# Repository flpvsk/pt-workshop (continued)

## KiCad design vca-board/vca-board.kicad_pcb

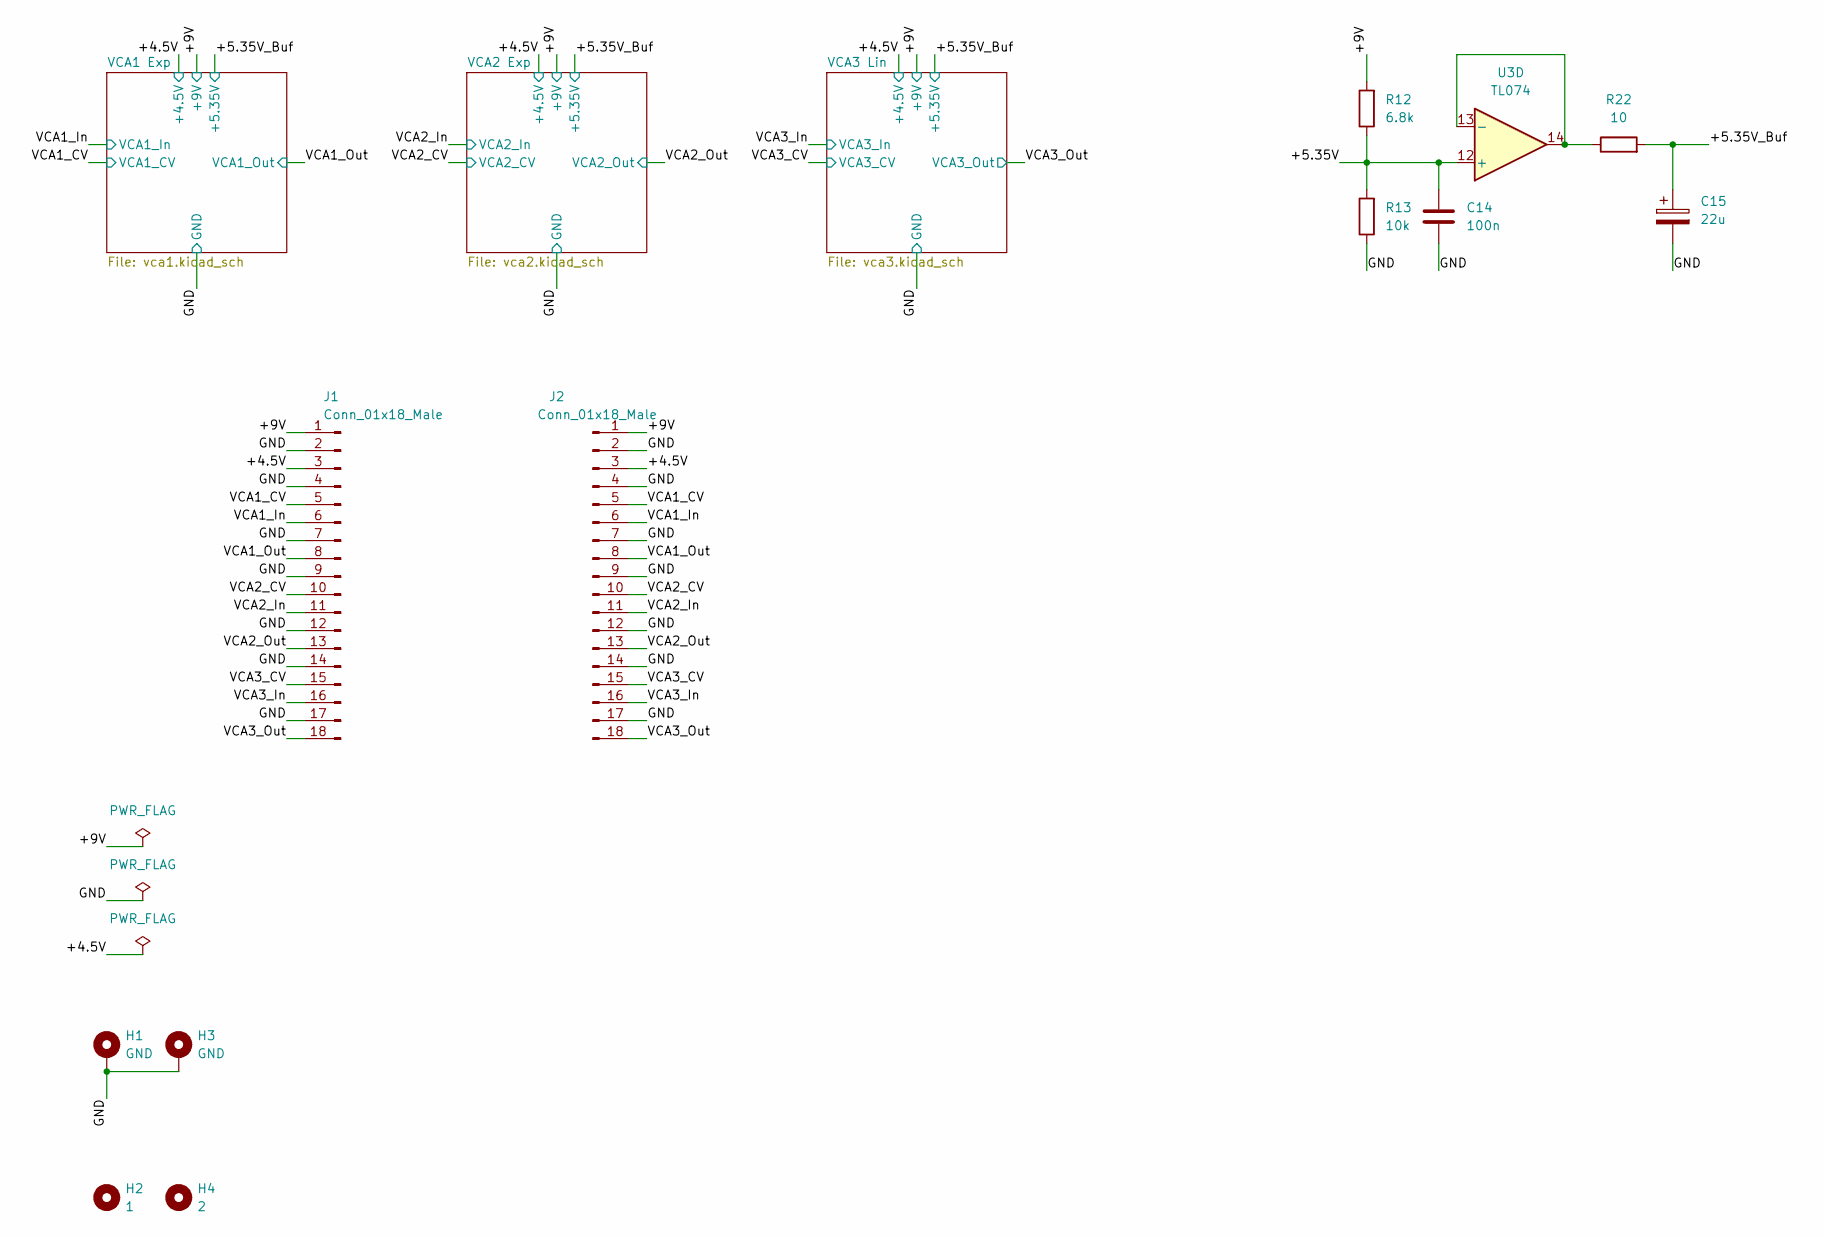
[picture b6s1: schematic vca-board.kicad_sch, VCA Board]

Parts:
C14: 100n; C_0603_1608Metric_Pad1.08x0.95mm_HandSolder; LCSC C76711
C15: 22u; CP_EIA-3216-18_Kemet-A_Pad1.58x1.35mm_HandSolder; LCSC C129272
H1, H3: GND; MountingHole_3.2mm_M3_ISO14580_Pad
H2: 1; MountingHole_3.2mm_M3
H4: 2; MountingHole_3.2mm_M3
J1, J2: Conn_01x18_Male; PinHeader_1x18_P2.54mm_Vertical
R12: 6.8k; R_0603_1608Metric_Pad0.98x0.95mm_HandSolder; LCSC C23212
R13: 10k; R_0603_1608Metric_Pad0.98x0.95mm_HandSolder; LCSC C25804
R22: 10; R_0603_1608Metric_Pad0.98x0.95mm_HandSolder; LCSC C22859
U3: TL074; SOIC-14_3.9x8.7mm_P1.27mm; LCSC C6963

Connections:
/+4.5V: J1.3, J2.3; also elsewhere on the board
/+5.35V: C14.2, R12.1, R13.2, U3.12 (+)
/+5.35V_Buf: C15.1, R22.2; also elsewhere on the board
/+9V: J1.1, J2.1, R12.2; also elsewhere on the board
/GND: C14.1, C15.2, H1.1, H3.1, J1.2, J1.4, J1.7, J1.9, J1.12, J1.14, J1.17, J2.2, J2.4, J2.7, J2.9, J2.12, J2.14, J2.17, R13.1; also elsewhere on the board
/VCA1_CV: J1.5, J2.5; also elsewhere on the board
/VCA1_In: J1.6, J2.6; also elsewhere on the board
/VCA1_Out: J1.8, J2.8; also elsewhere on the board
/VCA2_CV: J1.10, J2.10; also elsewhere on the board
/VCA2_In: J1.11, J2.11; also elsewhere on the board
/VCA2_Out: J1.13, J2.13; also elsewhere on the board
/VCA3_CV: J1.15, J2.15; also elsewhere on the board
/VCA3_In: J1.16, J2.16; also elsewhere on the board
/VCA3_Out: J1.18, J2.18; also elsewhere on the board
unnamed: R22.1, U3.13 (-), U3.14

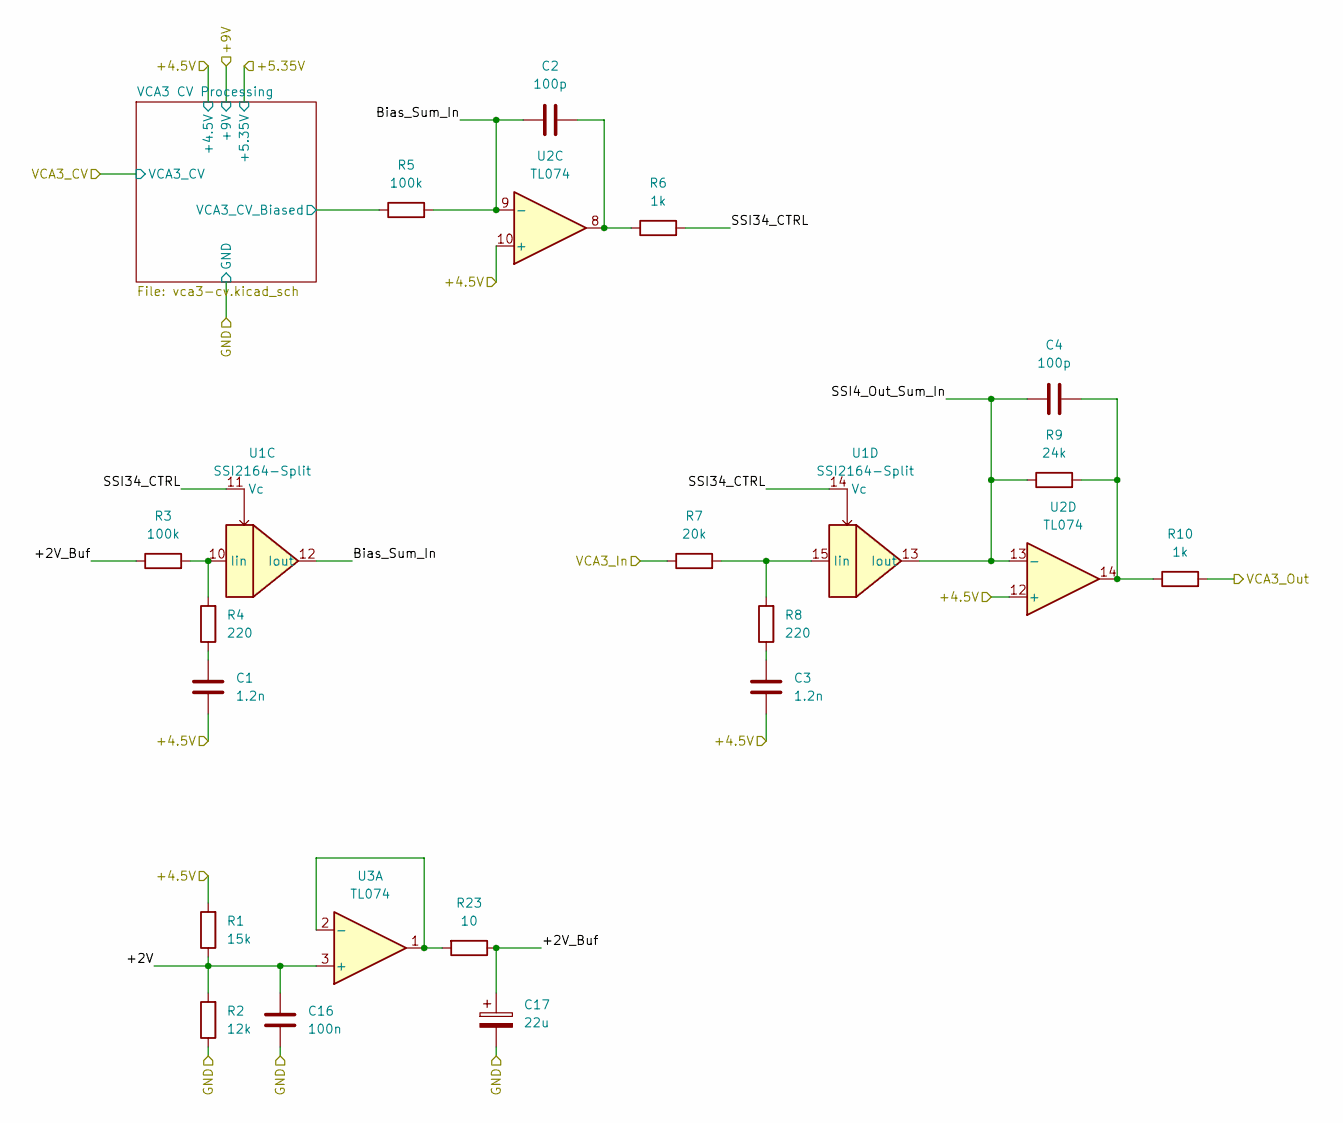
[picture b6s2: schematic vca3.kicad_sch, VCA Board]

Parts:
C1, C3: 1.2n; C_0603_1608Metric_Pad1.08x0.95mm_HandSolder; LCSC C576816
C2, C4: 100p; C_0603_1608Metric_Pad1.08x0.95mm_HandSolder; LCSC C160903
C16: 100n; C_0603_1608Metric_Pad1.08x0.95mm_HandSolder; LCSC C76711
C17: 22u; CP_EIA-3216-18_Kemet-A_Pad1.58x1.35mm_HandSolder; LCSC C129272
R1: 15k; R_0603_1608Metric_Pad0.98x0.95mm_HandSolder; LCSC C22809
R2: 12k; R_0603_1608Metric_Pad0.98x0.95mm_HandSolder; LCSC C22790
R3, R5: 100k; R_0603_1608Metric_Pad0.98x0.95mm_HandSolder; LCSC C25803
R4, R8: 220; R_0603_1608Metric_Pad0.98x0.95mm_HandSolder; LCSC C22962
R6, R10: 1k; R_0603_1608Metric_Pad0.98x0.95mm_HandSolder; LCSC C21190
R7: 20k; R_0603_1608Metric_Pad0.98x0.95mm_HandSolder; LCSC C4184
R9: 24k; R_0603_1608Metric_Pad0.98x0.95mm_HandSolder; LCSC C23352
R23: 10; R_0603_1608Metric_Pad0.98x0.95mm_HandSolder; LCSC C22859
U1: SSI2164-Split; SOIC-16_3.9x9.9mm_P1.27mm
U2, U3: TL074; SOIC-14_3.9x8.7mm_P1.27mm; LCSC C6963

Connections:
/+4.5V: C1.1, C3.1, R1.2, U2.10 (+), U2.12 (+); also elsewhere on the board
/GND: C16.1, C17.2, R2.1; also elsewhere on the board
/VCA3 Lin/+2V: C16.2, R1.1, R2.2, U3.3 (+)
/VCA3 Lin/+2V_Buf: C17.1, R3.1, R23.1
/VCA3 Lin/Bias_Sum_In: C2.1, R5.2, U1.12 (Iout), U2.9 (-)
/VCA3 Lin/SSI4_Out_Sum_In: C4.2, R9.1, U1.13 (Iout), U2.13 (-)
/VCA3 Lin/SSI34_CTRL: R6.2, U1.11 (Vc), U1.14 (Vc)
/VCA3 Lin/VCA3 CV Processing/VCA3_CV_Biased: R5.1; also elsewhere on the board
/VCA3_In: R7.1; also elsewhere on the board
/VCA3_Out: R10.2; also elsewhere on the board
unnamed: C1.2, R4.1
unnamed: C2.2, R6.1, U2.8
unnamed: C3.2, R8.1
unnamed: C4.1, R9.2, R10.1, U2.14
unnamed: R3.2, R4.2, U1.10 (Iin)
unnamed: R7.2, R8.2, U1.15 (Iin)
unnamed: R23.2, U3.1, U3.2 (-)

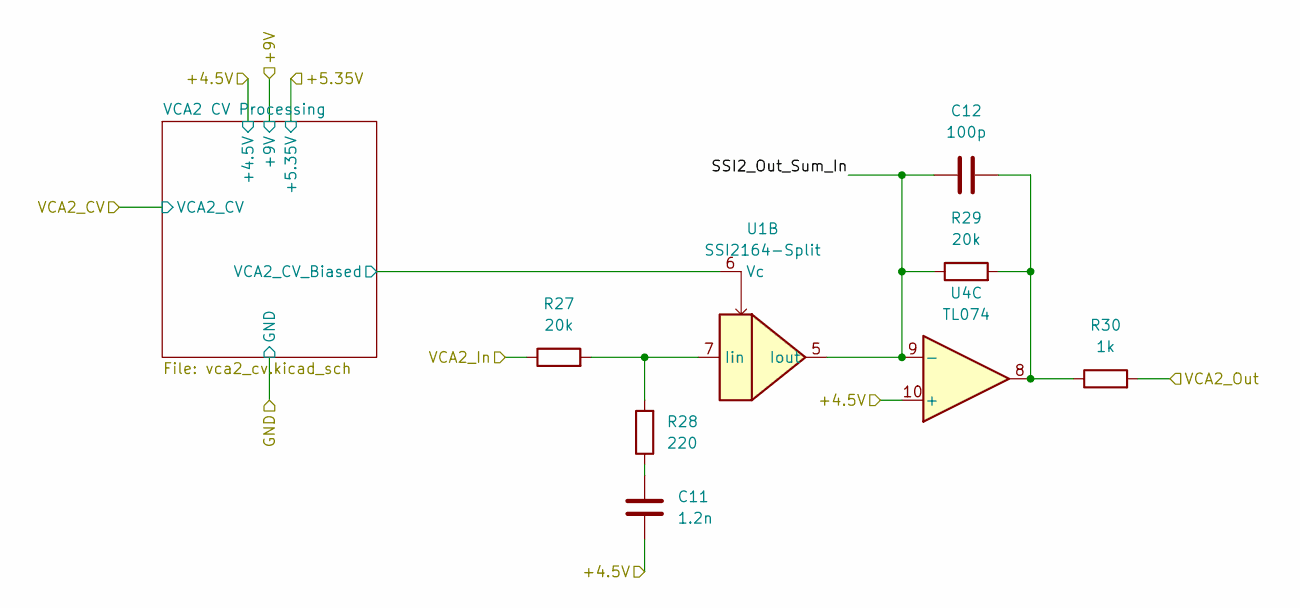
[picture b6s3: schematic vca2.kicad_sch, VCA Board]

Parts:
C11: 1.2n; C_0603_1608Metric_Pad1.08x0.95mm_HandSolder; LCSC C576816
C12: 100p; C_0603_1608Metric_Pad1.08x0.95mm_HandSolder; LCSC C160903
R27, R29: 20k; R_0603_1608Metric_Pad0.98x0.95mm_HandSolder; LCSC C4184
R28: 220; R_0603_1608Metric_Pad0.98x0.95mm_HandSolder; LCSC C22962
R30: 1k; R_0603_1608Metric_Pad0.98x0.95mm_HandSolder; LCSC C21190
U1: SSI2164-Split; SOIC-16_3.9x9.9mm_P1.27mm
U4: TL074; SOIC-14_3.9x8.7mm_P1.27mm; LCSC C6963

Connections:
/+4.5V: C11.1, U4.10 (+); also elsewhere on the board
/VCA2 Exp/SSI2_Out_Sum_In: C12.2, R29.1, U1.5 (Iout), U4.9 (-)
/VCA2 Exp/VCA2 CV Processing/VCA2_CV_Biased: U1.6 (Vc); also elsewhere on the board
/VCA2_In: R27.1; also elsewhere on the board
/VCA2_Out: R30.2; also elsewhere on the board
unnamed: C11.2, R28.1
unnamed: C12.1, R29.2, R30.1, U4.8
unnamed: R27.2, R28.2, U1.7 (Iin)

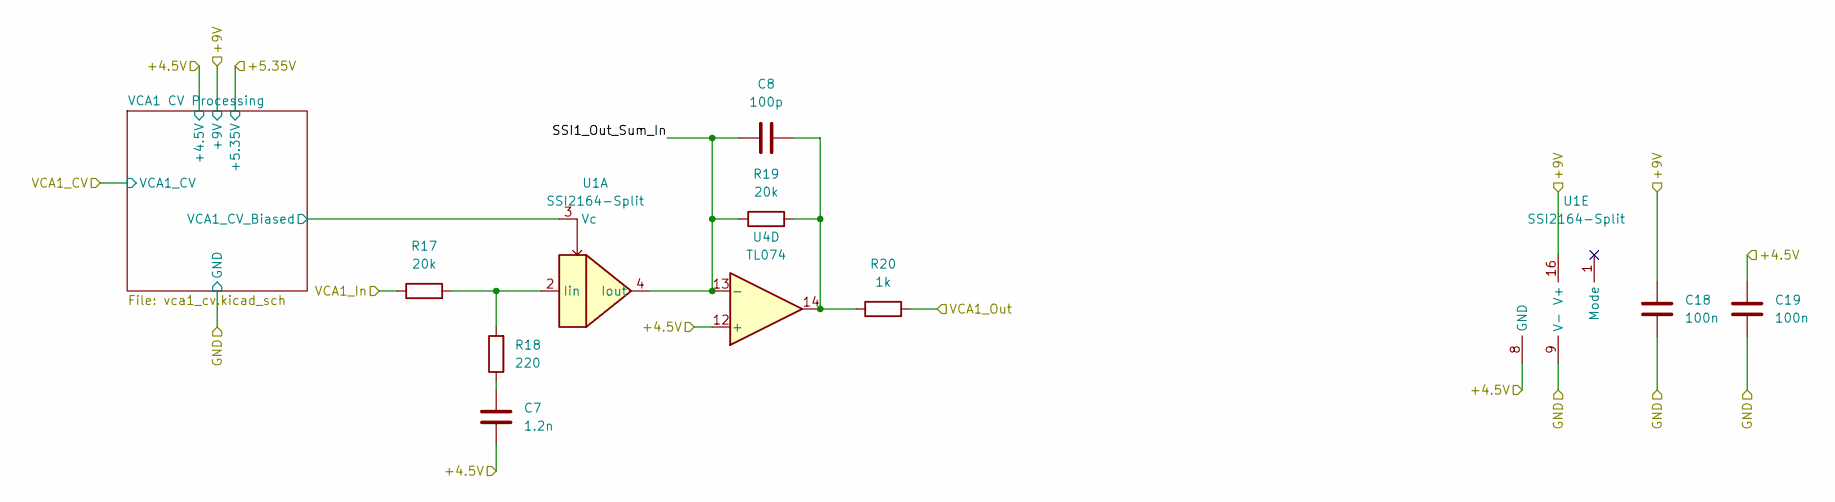
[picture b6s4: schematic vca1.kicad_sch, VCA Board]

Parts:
C7: 1.2n; C_0603_1608Metric_Pad1.08x0.95mm_HandSolder; LCSC C576816
C8: 100p; C_0603_1608Metric_Pad1.08x0.95mm_HandSolder; LCSC C160903
C18, C19: 100n; C_0603_1608Metric_Pad1.08x0.95mm_HandSolder; LCSC C76711
R17, R19: 20k; R_0603_1608Metric_Pad0.98x0.95mm_HandSolder; LCSC C4184
R18: 220; R_0603_1608Metric_Pad0.98x0.95mm_HandSolder; LCSC C22962
R20: 1k; R_0603_1608Metric_Pad0.98x0.95mm_HandSolder; LCSC C21190
U1: SSI2164-Split; SOIC-16_3.9x9.9mm_P1.27mm
U4: TL074; SOIC-14_3.9x8.7mm_P1.27mm; LCSC C6963

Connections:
/+4.5V: C7.1, C19.2, U1.8 (GND), U4.12 (+); also elsewhere on the board
/+9V: C18.2, U1.16 (V+); also elsewhere on the board
/GND: C18.1, C19.1, U1.9 (V-); also elsewhere on the board
/VCA1 Exp/SSI1_Out_Sum_In: C8.2, R19.1, U1.4 (Iout), U4.13 (-)
/VCA1 Exp/VCA1 CV Processing/VCA1_CV_Biased: U1.3 (Vc); also elsewhere on the board
/VCA1_In: R17.1; also elsewhere on the board
/VCA1_Out: R20.2; also elsewhere on the board
unnamed: C7.2, R18.1
unnamed: C8.1, R19.2, R20.1, U4.14
unnamed: R17.2, R18.2, U1.2 (Iin)

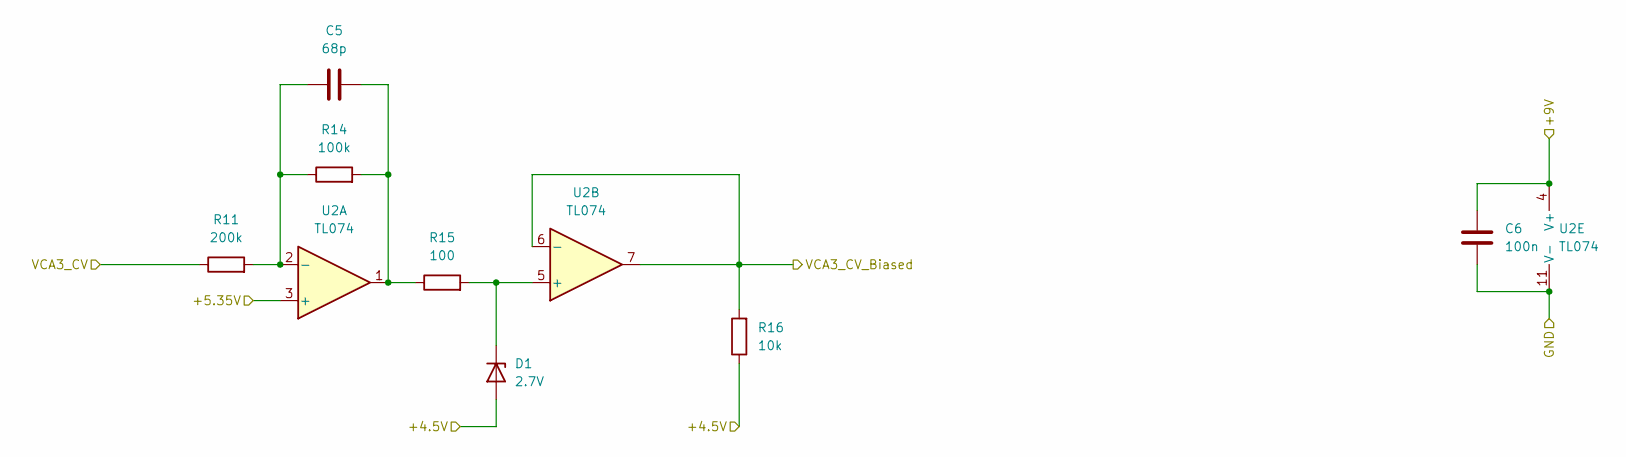
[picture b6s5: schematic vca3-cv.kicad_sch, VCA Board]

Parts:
C5: 68p; C_0603_1608Metric_Pad1.08x0.95mm_HandSolder; LCSC C1680
C6: 100n; C_0603_1608Metric_Pad1.08x0.95mm_HandSolder; LCSC C76711
D1: 2.7V; D_SOD-123; LCSC C406712
R11: 200k; R_0603_1608Metric_Pad0.98x0.95mm_HandSolder; LCSC C25811
R14: 100k; R_0603_1608Metric_Pad0.98x0.95mm_HandSolder; LCSC C25803
R15: 100; R_0603_1608Metric_Pad0.98x0.95mm_HandSolder; LCSC C22775
R16: 10k; R_0603_1608Metric_Pad0.98x0.95mm_HandSolder; LCSC C25804
U2: TL074; SOIC-14_3.9x8.7mm_P1.27mm; LCSC C6963

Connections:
/+4.5V: D1.2 (A), R16.1; also elsewhere on the board
/+5.35V_Buf: U2.3 (+); also elsewhere on the board
/+9V: C6.2, U2.4 (V+); also elsewhere on the board
/GND: C6.1, U2.11 (V-); also elsewhere on the board
/VCA3 Lin/VCA3 CV Processing/VCA3_CV_Biased: R16.2, U2.6 (-), U2.7; also elsewhere on the board
/VCA3_CV: R11.1; also elsewhere on the board
unnamed: C5.1, R11.2, R14.1, U2.2 (-)
unnamed: C5.2, R14.2, R15.1, U2.1
unnamed: D1.1 (K), R15.2, U2.5 (+)

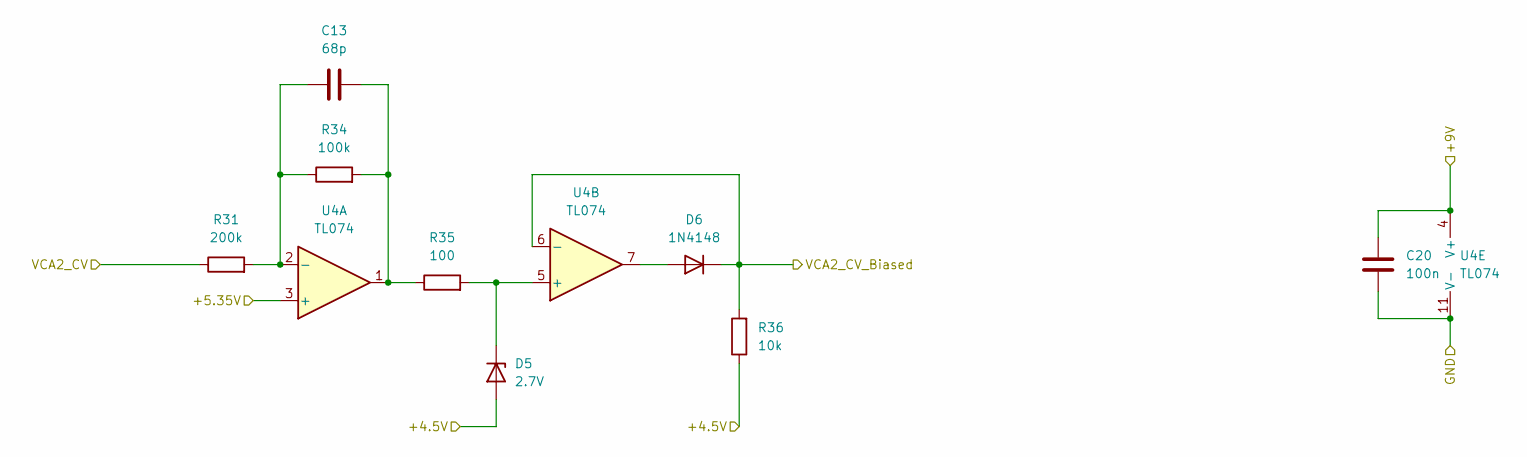
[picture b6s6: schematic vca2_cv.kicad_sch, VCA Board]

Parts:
C13: 68p; C_0603_1608Metric_Pad1.08x0.95mm_HandSolder; LCSC C1680
C20: 100n; C_0603_1608Metric_Pad1.08x0.95mm_HandSolder; LCSC C76711
D5: 2.7V; D_SOD-123; LCSC C406712
D6: 1N4148; D_SOD-123; LCSC C81598
R31: 200k; R_0603_1608Metric_Pad0.98x0.95mm_HandSolder; LCSC C25811
R34: 100k; R_0603_1608Metric_Pad0.98x0.95mm_HandSolder; LCSC C25803
R35: 100; R_0603_1608Metric_Pad0.98x0.95mm_HandSolder; LCSC C22775
R36: 10k; R_0603_1608Metric_Pad0.98x0.95mm_HandSolder; LCSC C25804
U4: TL074; SOIC-14_3.9x8.7mm_P1.27mm; LCSC C6963

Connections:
/+4.5V: D5.2 (A), R36.1; also elsewhere on the board
/+5.35V_Buf: U4.3 (+); also elsewhere on the board
/+9V: C20.2, U4.4 (V+); also elsewhere on the board
/GND: C20.1, U4.11 (V-); also elsewhere on the board
/VCA2 Exp/VCA2 CV Processing/VCA2_CV_Biased: D6.1 (K), R36.2, U4.6 (-); also elsewhere on the board
/VCA2_CV: R31.1; also elsewhere on the board
unnamed: C13.1, R31.2, R34.1, U4.2 (-)
unnamed: C13.2, R34.2, R35.1, U4.1
unnamed: D5.1 (K), R35.2, U4.5 (+)
unnamed: D6.2 (A), U4.7

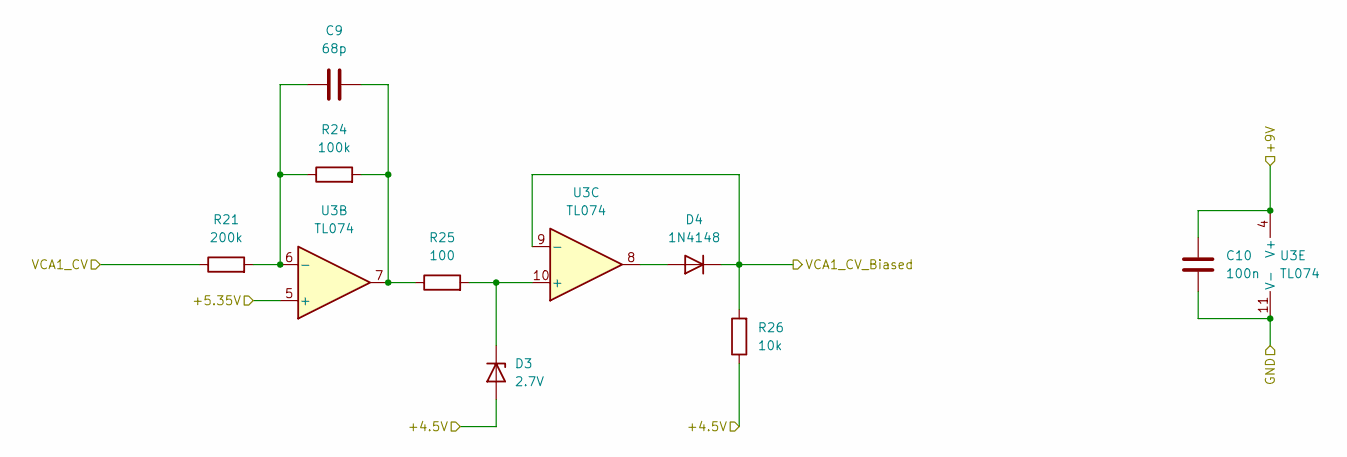
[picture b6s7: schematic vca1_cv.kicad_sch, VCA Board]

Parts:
C9: 68p; C_0603_1608Metric_Pad1.08x0.95mm_HandSolder; LCSC C1680
C10: 100n; C_0603_1608Metric_Pad1.08x0.95mm_HandSolder; LCSC C76711
D3: 2.7V; D_SOD-123; LCSC C406712
D4: 1N4148; D_SOD-123; LCSC C81598
R21: 200k; R_0603_1608Metric_Pad0.98x0.95mm_HandSolder; LCSC C25811
R24: 100k; R_0603_1608Metric_Pad0.98x0.95mm_HandSolder; LCSC C25803
R25: 100; R_0603_1608Metric_Pad0.98x0.95mm_HandSolder; LCSC C22775
R26: 10k; R_0603_1608Metric_Pad0.98x0.95mm_HandSolder; LCSC C25804
U3: TL074; SOIC-14_3.9x8.7mm_P1.27mm; LCSC C6963

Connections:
/+4.5V: D3.2 (A), R26.1; also elsewhere on the board
/+5.35V_Buf: U3.5 (+); also elsewhere on the board
/+9V: C10.2, U3.4 (V+); also elsewhere on the board
/GND: C10.1, U3.11 (V-); also elsewhere on the board
/VCA1 Exp/VCA1 CV Processing/VCA1_CV_Biased: D4.1 (K), R26.2, U3.9 (-); also elsewhere on the board
/VCA1_CV: R21.1; also elsewhere on the board
unnamed: C9.1, R21.2, R24.1, U3.6 (-)
unnamed: C9.2, R24.2, R25.1, U3.7
unnamed: D3.1 (K), R25.2, U3.10 (+)
unnamed: D4.2 (A), U3.8

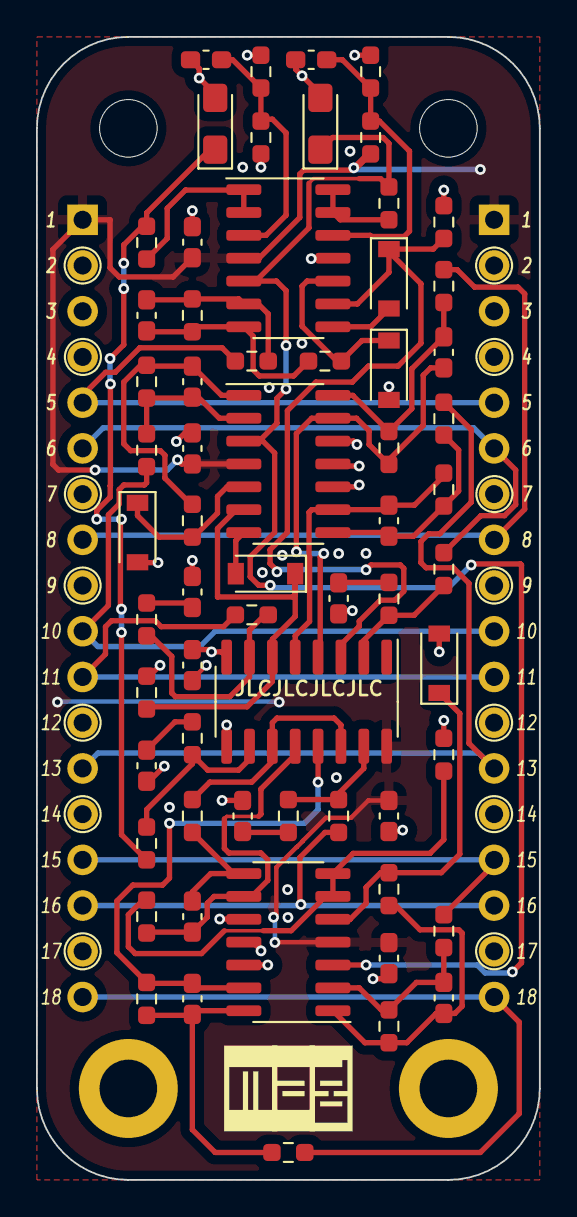
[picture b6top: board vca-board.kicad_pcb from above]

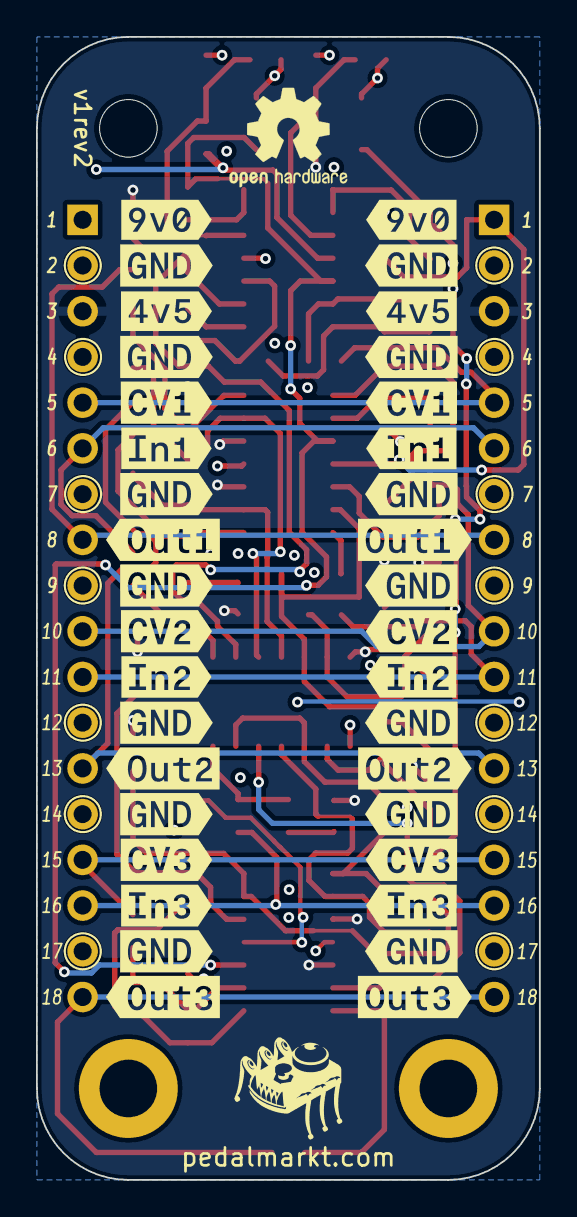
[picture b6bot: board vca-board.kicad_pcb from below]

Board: 4 copper layers, 27.9 x 63.5 mm, 106 parts (38 on the bottom side), 49 nets.

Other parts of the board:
kibuzzard-666B18FD: G***; kibuzzard-666B18FD
kibuzzard-672CA2A2: G***; kibuzzard-672CA2A2
kibuzzard-672CA10D: G***; kibuzzard-672CA10D
kibuzzard-672CA11C: G***; kibuzzard-672CA11C
kibuzzard-672CA12F: G***; kibuzzard-672CA12F
kibuzzard-672CA13C: G***; kibuzzard-672CA13C
kibuzzard-672CA14B: G***; kibuzzard-672CA14B
kibuzzard-672CA14F: G***; kibuzzard-672CA14F
kibuzzard-672CA15D: G***; kibuzzard-672CA15D
kibuzzard-672CA24E: G***; kibuzzard-672CA24E
kibuzzard-672CA25B: G***; kibuzzard-672CA25B
kibuzzard-672CA26A: G***; kibuzzard-672CA26A
kibuzzard-672CA26E: G***; kibuzzard-672CA26E
kibuzzard-672CA27B: G***; kibuzzard-672CA27B
kibuzzard-672CA28C: G***; kibuzzard-672CA28C
kibuzzard-672CA29D: G***; kibuzzard-672CA29D
kibuzzard-672CA102: G***; kibuzzard-672CA102
kibuzzard-672CA109: G***; kibuzzard-672CA109
kibuzzard-672CA113: G***; kibuzzard-672CA113
kibuzzard-672CA118: G***; kibuzzard-672CA118
kibuzzard-672CA121: G***; kibuzzard-672CA121
kibuzzard-672CA129: G***; kibuzzard-672CA129
kibuzzard-672CA136: G***; kibuzzard-672CA136
kibuzzard-672CA140: G***; kibuzzard-672CA140
kibuzzard-672CA146: G***; kibuzzard-672CA146
kibuzzard-672CA156: G***; kibuzzard-672CA156
kibuzzard-672CA162: G***; kibuzzard-672CA162
kibuzzard-672CA252: G***; kibuzzard-672CA252
kibuzzard-672CA257: G***; kibuzzard-672CA257
kibuzzard-672CA260: G***; kibuzzard-672CA260
kibuzzard-672CA266: G***; kibuzzard-672CA266
kibuzzard-672CA275: G***; kibuzzard-672CA275
kibuzzard-672CA280: G***; kibuzzard-672CA280
kibuzzard-672CA284: G***; kibuzzard-672CA284
kibuzzard-672CA288: G***; kibuzzard-672CA288
kibuzzard-672CA293: G***; kibuzzard-672CA293
kibuzzard-672CA298: G***; kibuzzard-672CA298

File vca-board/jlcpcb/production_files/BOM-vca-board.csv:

Comment,Designator,Footprint,LCSC
22u,"C15,C17",CP_EIA-3216-18_Kemet-A_Pad1.58x1.35mm_HandSolder,C129272
100p,"C12,C2,C4,C8",C_0603_1608Metric_Pad1.08x0.95mm_HandSolder,C160903
68p,"C13,C5,C9",C_0603_1608Metric_Pad1.08x0.95mm_HandSolder,C1680
1k,"R10,R20,R30,R6",R_0603_1608Metric_Pad0.98x0.95mm_HandSolder,C21190
100,"R15,R25,R35",R_0603_1608Metric_Pad0.98x0.95mm_HandSolder,C22775
12k,R2,R_0603_1608Metric_Pad0.98x0.95mm_HandSolder,C22790
15k,R1,R_0603_1608Metric_Pad0.98x0.95mm_HandSolder,C22809
10,"R22,R23",R_0603_1608Metric_Pad0.98x0.95mm_HandSolder,C22859
220,"R18,R28,R4,R8",R_0603_1608Metric_Pad0.98x0.95mm_HandSolder,C22962
6.8k,R12,R_0603_1608Metric_Pad0.98x0.95mm_HandSolder,C23212
24k,R9,R_0603_1608Metric_Pad0.98x0.95mm_HandSolder,C23352
100k,"R14,R24,R3,R34,R5",R_0603_1608Metric_Pad0.98x0.95mm_HandSolder,C25803
10k,"R13,R16,R26,R36",R_0603_1608Metric_Pad0.98x0.95mm_HandSolder,C25804
200k,"R11,R21,R31",R_0603_1608Metric_Pad0.98x0.95mm_HandSolder,C25811
2.7V,"D1,D3,D5",D_SOD-123,C406712
20k,"R17,R19,R27,R29,R7",R_0603_1608Metric_Pad0.98x0.95mm_HandSolder,C4184
1.2n,"C1,C11,C3,C7",C_0603_1608Metric_Pad1.08x0.95mm_HandSolder,C576816
TL074,"U2,U3,U4",SOIC-14_3.9x8.7mm_P1.27mm,C6963
100n,"C10,C14,C16,C18,C19,C20,C6",C_0603_1608Metric_Pad1.08x0.95mm_HandSolder,C76711
1N4148,"D4,D6",D_SOD-123,C81598
GND,H3,MountingHole_3.2mm_M3_ISO14580_Pad,
2,H4,MountingHole_3.2mm_M3,
1,H2,MountingHole_3.2mm_M3,
SSI2164-Split,U1,SOIC-16_3.9x9.9mm_P1.27mm,
GND,H1,MountingHole_3.2mm_M3_ISO14580_Pad,
Conn_01x18_Male,J2,PinHeader_1x18_P2.54mm_Vertical,
Conn_01x18_Male,J1,PinHeader_1x18_P2.54mm_Vertical,

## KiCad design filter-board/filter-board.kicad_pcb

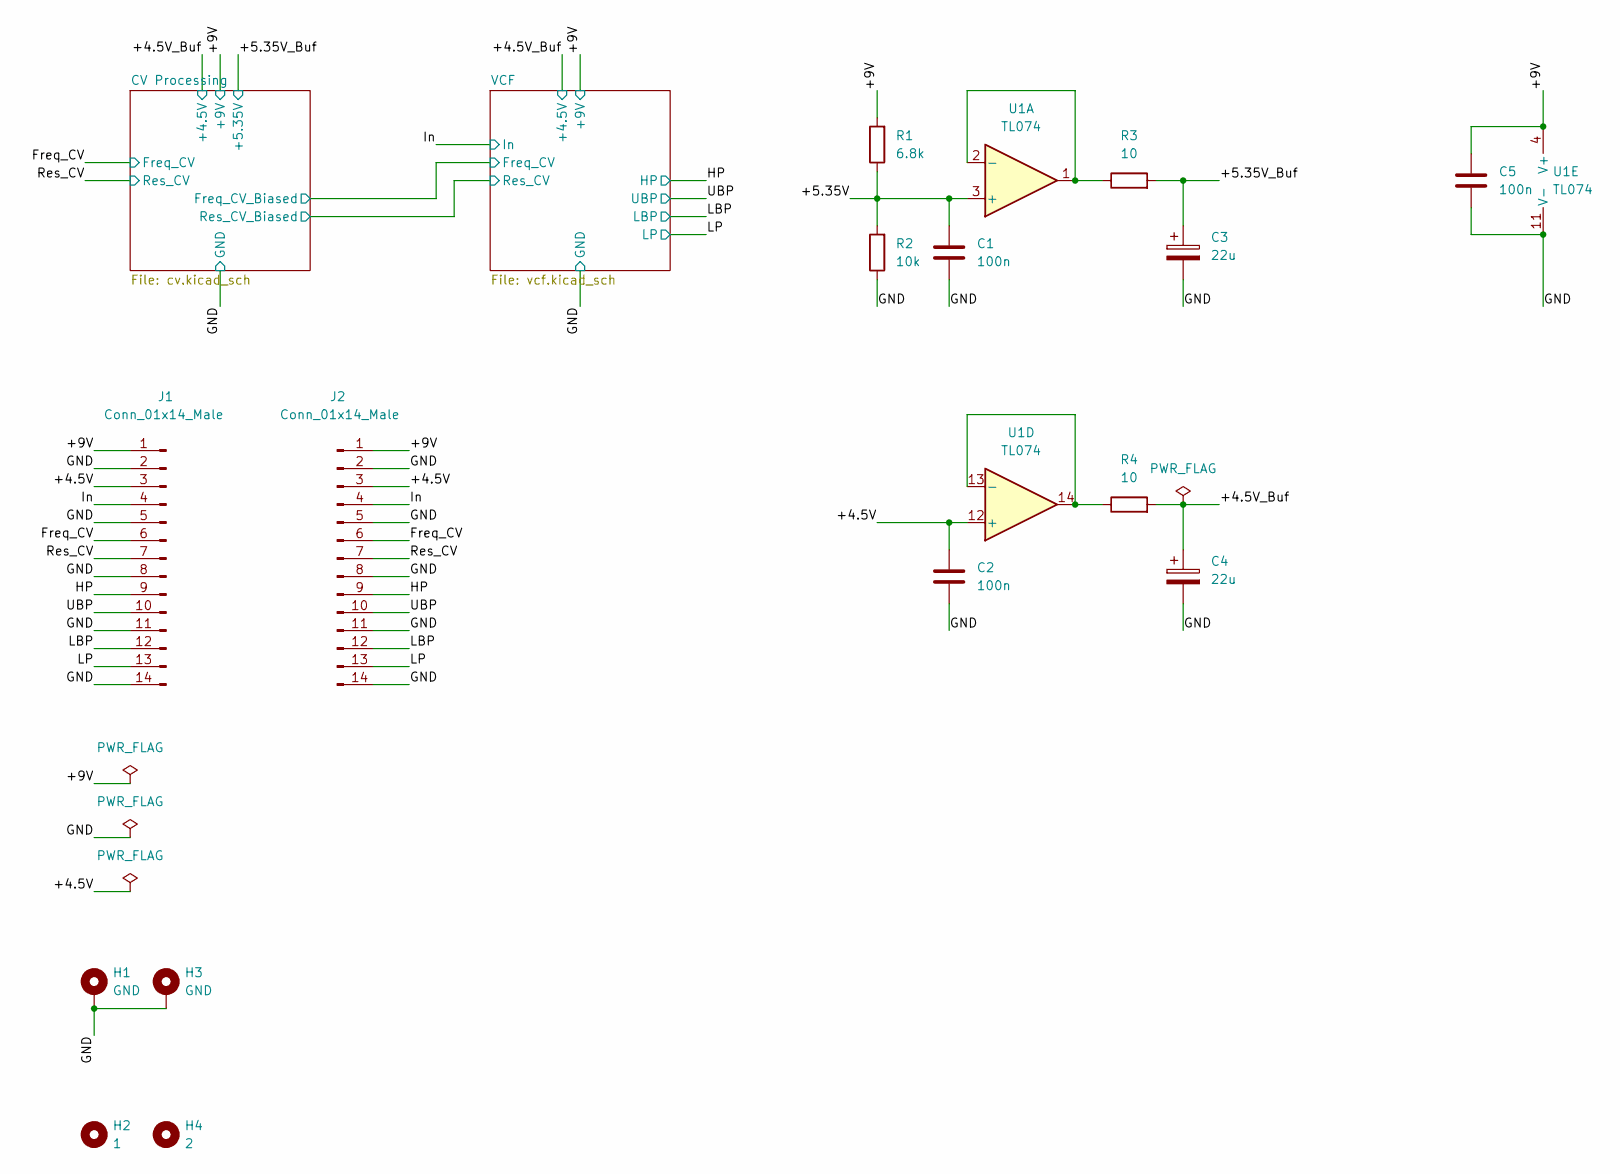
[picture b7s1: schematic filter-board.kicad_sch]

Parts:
C1, C2, C5: 100n; C_0603_1608Metric_Pad1.08x0.95mm_HandSolder; LCSC C76711
C3, C4: 22u; CP_EIA-3216-18_Kemet-A_Pad1.58x1.35mm_HandSolder; LCSC C129272
H1, H3: GND; MountingHole_3.2mm_M3_ISO14580_Pad
H2: 1; MountingHole_3.2mm_M3
H4: 2; MountingHole_3.2mm_M3
J1, J2: Conn_01x14_Male; PinHeader_1x14_P2.54mm_Vertical
R1: 6.8k; R_0603_1608Metric_Pad0.98x0.95mm_HandSolder; LCSC C23212
R2: 10k; R_0603_1608Metric_Pad0.98x0.95mm_HandSolder; LCSC C25804
R3, R4: 10; R_0603_1608Metric_Pad0.98x0.95mm_HandSolder; LCSC C22859
U1: TL074; SOIC-14_3.9x8.7mm_P1.27mm; LCSC C6963

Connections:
/+4.5V: C2.2, J1.3, J2.3, U1.12 (+)
/+4.5V_Buf: C4.1, R4.2; also elsewhere on the board
/+5.35V: C1.2, R1.1, R2.2, U1.3 (+)
/+5.35V_Buf: C3.1, R3.2; also elsewhere on the board
/+9V: C5.1, J1.1, J2.1, R1.2, U1.4 (V+); also elsewhere on the board
/Freq_CV: J1.6, J2.6; also elsewhere on the board
/GND: C1.1, C2.1, C3.2, C4.2, C5.2, H1.1, H3.1, J1.2, J1.5, J1.8, J1.11, J1.14, J2.2, J2.5, J2.8, J2.11, J2.14, R2.1, U1.11 (V-); also elsewhere on the board
/HP: J1.9, J2.9; also elsewhere on the board
/In: J1.4, J2.4; also elsewhere on the board
/LBP: J1.12, J2.12; also elsewhere on the board
/LP: J1.13, J2.13; also elsewhere on the board
/Res_CV: J1.7, J2.7; also elsewhere on the board
/UBP: J1.10, J2.10; also elsewhere on the board
unnamed: R3.1, U1.1, U1.2 (-)
unnamed: R4.1, U1.13 (-), U1.14

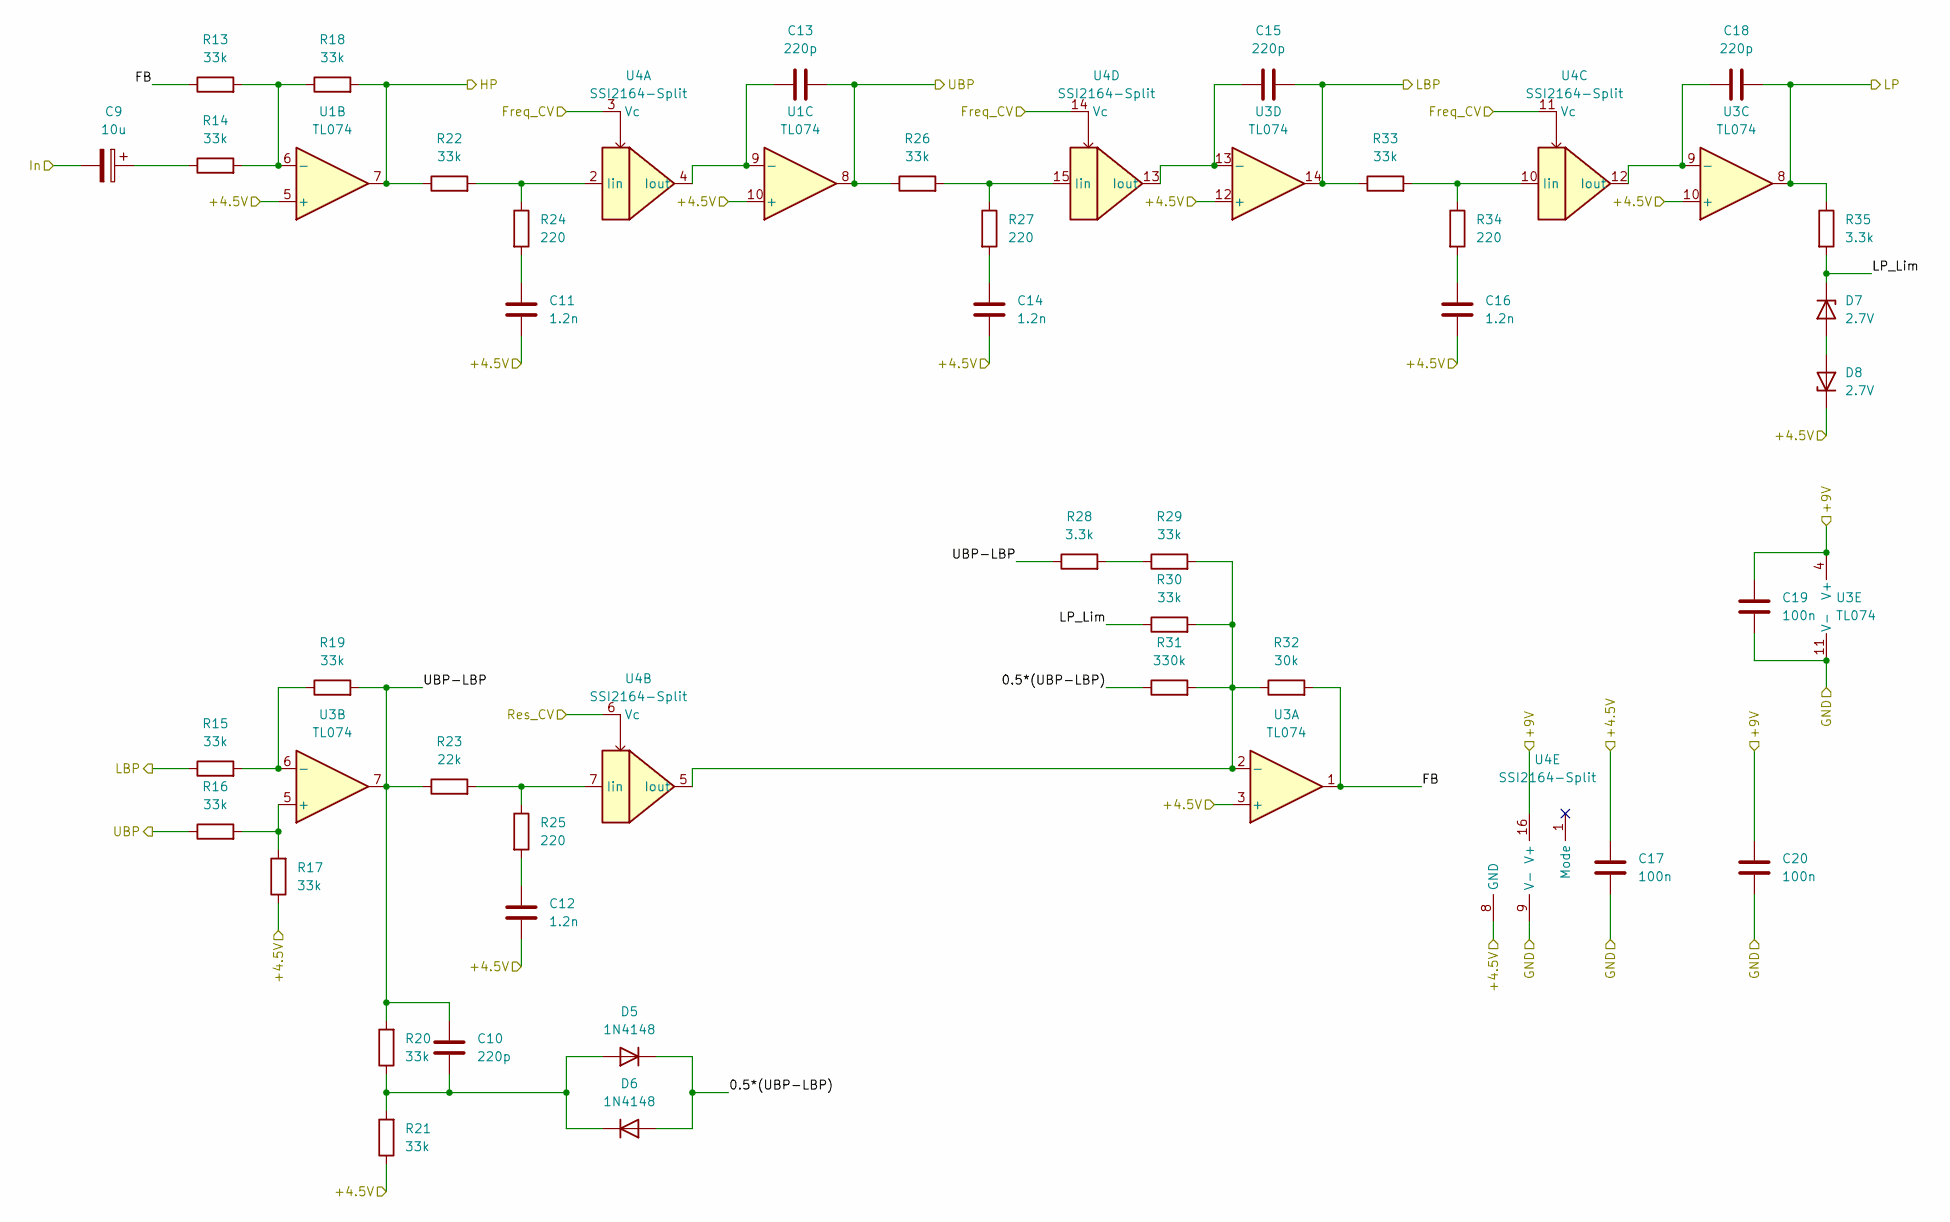
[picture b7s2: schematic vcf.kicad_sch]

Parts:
C9: 10u; CP_Elec_5x5.4; LCSC C72486
C10, C13, C15, C18: 220p; C_0603_1608Metric_Pad1.08x0.95mm_HandSolder; LCSC C106210
C11, C12, C14, C16: 1.2n; C_0603_1608Metric_Pad1.08x0.95mm_HandSolder; LCSC C576816
C17, C19, C20: 100n; C_0603_1608Metric_Pad1.08x0.95mm_HandSolder; LCSC C76711
D5, D6: 1N4148; D_SOD-123; LCSC C81598
D7, D8: 2.7V; D_SOD-123; LCSC C406712
R13, R14, R15, R16, R17, R18, R19, R20, R21, R22, R26, R29, R30, R33: 33k; R_0603_1608Metric_Pad0.98x0.95mm_HandSolder; LCSC C4216
R23: 22k; R_0603_1608Metric_Pad0.98x0.95mm_HandSolder; LCSC C31850
R24, R25, R27, R34: 220; R_0603_1608Metric_Pad0.98x0.95mm_HandSolder; LCSC C22962
R28, R35: 3.3k; R_0603_1608Metric_Pad0.98x0.95mm_HandSolder; LCSC C22978
R31: 330k; R_0603_1608Metric_Pad0.98x0.95mm_HandSolder; LCSC C23137
R32: 30k; R_0603_1608Metric_Pad0.98x0.95mm_HandSolder; LCSC C22984
U1, U3: TL074; SOIC-14_3.9x8.7mm_P1.27mm; LCSC C6963
U4: SSI2164-Split; SOIC-16_3.9x9.9mm_P1.27mm

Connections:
/+4.5V_Buf: C11.2, C12.2, C14.2, C16.2, C17.1, D8.1 (K), R17.1, R21.1, U1.5 (+), U1.10 (+), U3.3 (+), U3.10 (+), U3.12 (+), U4.8 (GND); also elsewhere on the board
/+9V: C19.1, C20.1, U3.4 (V+), U4.16 (V+); also elsewhere on the board
/CV Processing/Freq_CV_Biased: U4.3 (Vc), U4.11 (Vc), U4.14 (Vc); also elsewhere on the board
/CV Processing/Res_CV_Biased: U4.6 (Vc); also elsewhere on the board
/GND: C17.2, C19.2, C20.2, U3.11 (V-), U4.9 (V-); also elsewhere on the board
/HP: R18.2, R22.1, U1.7; also elsewhere on the board
/In: C9.2; also elsewhere on the board
/LBP: C15.2, R15.1, R33.1, U3.14; also elsewhere on the board
/LP: C18.2, R35.1, U3.8; also elsewhere on the board
/UBP: C13.2, R16.1, R26.1, U1.8; also elsewhere on the board
/VCF/0.5*(UBP-LBP): D5.1 (K), D6.2 (A), R31.1
/VCF/FB: R13.1, R32.2, U3.1
/VCF/LP_Lim: D7.1 (K), R30.1, R35.2
/VCF/UBP-LBP: C10.2, R19.2, R20.2, R23.1, R28.1, U3.7
unnamed: C9.1, R14.1
unnamed: C10.1, D5.2 (A), D6.1 (K), R20.1, R21.2
unnamed: C11.1, R24.2
unnamed: C12.1, R25.2
unnamed: C13.1, U1.9 (-), U4.4 (Iout)
unnamed: C14.1, R27.2
unnamed: C15.1, U3.13 (-), U4.13 (Iout)
unnamed: C16.1, R34.2
unnamed: C18.1, U3.9 (-), U4.12 (Iout)
unnamed: D7.2 (A), D8.2 (A)
unnamed: R13.2, R14.2, R18.1, U1.6 (-)
unnamed: R15.2, R19.1, U3.6 (-)
unnamed: R16.2, R17.2, U3.5 (+)
unnamed: R22.2, R24.1, U4.2 (Iin)
unnamed: R23.2, R25.1, U4.7 (Iin)
unnamed: R26.2, R27.1, U4.15 (Iin)
unnamed: R28.2, R29.1
unnamed: R29.2, R30.2, R31.2, R32.1, U3.2 (-), U4.5 (Iout)
unnamed: R33.2, R34.1, U4.10 (Iin)
